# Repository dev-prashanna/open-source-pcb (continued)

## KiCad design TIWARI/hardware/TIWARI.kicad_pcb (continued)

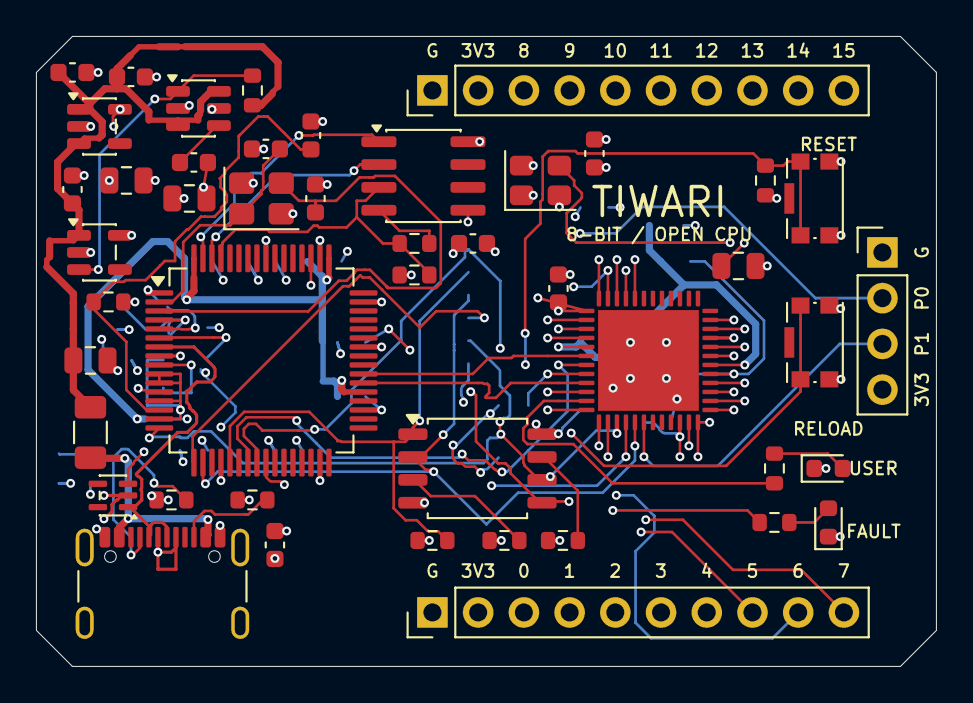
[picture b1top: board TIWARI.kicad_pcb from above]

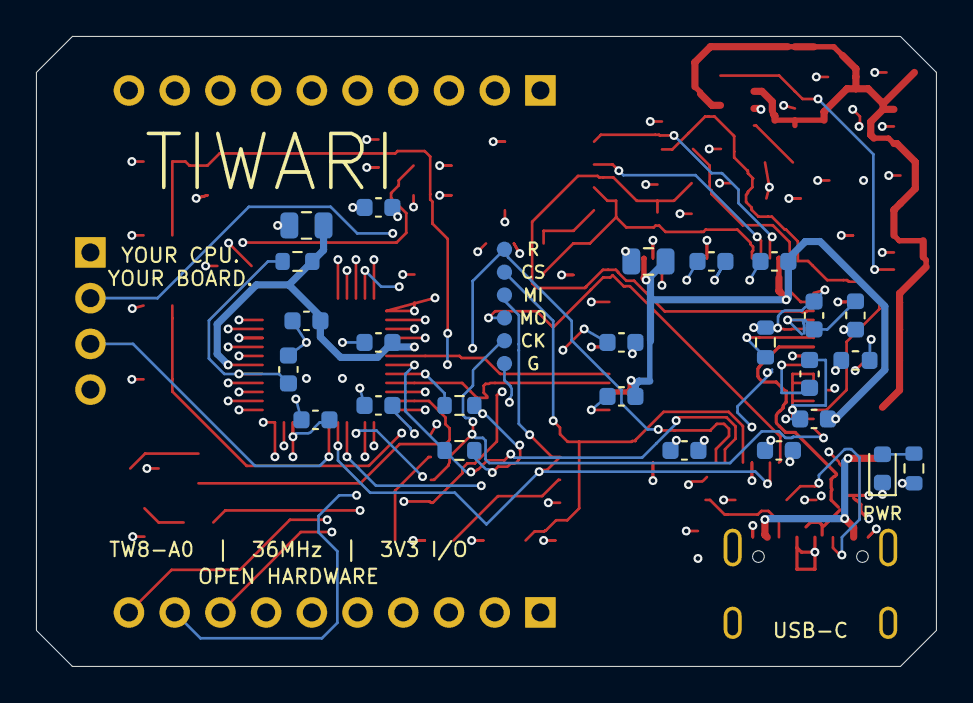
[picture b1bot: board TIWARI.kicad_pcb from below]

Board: 4 copper layers, 50.0 x 35.0 mm, 72 parts (26 on the bottom side), 58 nets.

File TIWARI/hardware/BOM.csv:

Reference,Value,MPN,Manufacturer,Footprint,Section,Datasheet
J1,USB4105-GF-A,USB4105-GF-A,GCT,Connector_USB:USB_C_Receptacle_GCT_USB4105-xx-A_16P_TopMnt_Horizontal,USB-C and Sequenced Power,https://gct.co/connector/usb4105
R1,5.1k,RC0603FR-075K1L,Yageo,Resistor_SMD:R_0603_1608Metric,USB-C and Sequenced Power,
R2,5.1k,RC0603FR-075K1L,Yageo,Resistor_SMD:R_0603_1608Metric,USB-C and Sequenced Power,
F1,500mA,1206L050YR,Littelfuse,Fuse:Fuse_1206_3216Metric,USB-C and Sequenced Power,
U3,AP2112K-1.2TRG1,AP2112K-1.2TRG1,Diodes Incorporated,Package_TO_SOT_SMD:SOT-23-5,USB-C and Sequenced Power,https://www.diodes.com/datasheet/download/AP2112.pdf
U4,AP2112K-3.3TRG1,AP2112K-3.3TRG1,Diodes Incorporated,Package_TO_SOT_SMD:SOT-23-5,USB-C and Sequenced Power,https://www.diodes.com/datasheet/download/AP2112.pdf
U5,TPS3808G12DBVR,TPS3808G12DBVR,Texas Instruments,Package_TO_SOT_SMD:SOT-23-6,USB-C and Sequenced Power,https://www.ti.com/lit/ds/symlink/tps3808.pdf
R3,10k,RC0603FR-0710KL,Yageo,Resistor_SMD:R_0603_1608Metric,USB-C and Sequenced Power,
C1,10n,GRM188R71H103KA01D,Murata,Capacitor_SMD:C_0603_1608Metric,USB-C and Sequenced Power,
C2,1u,GRM188R61A105KA61D,Murata,Capacitor_SMD:C_0603_1608Metric,USB-C and Sequenced Power,
C3,4.7u,GRM21BR61A475KA73L,Murata,Capacitor_SMD:C_0805_2012Metric,USB-C and Sequenced Power,
C4,1u,GRM188R61A105KA61D,Murata,Capacitor_SMD:C_0603_1608Metric,USB-C and Sequenced Power,
C5,4.7u,GRM21BR61A475KA73L,Murata,Capacitor_SMD:C_0805_2012Metric,USB-C and Sequenced Power,
C6,100n,GRM188R71C104KA01D,Murata,Capacitor_SMD:C_0603_1608Metric,USB-C and Sequenced Power,
C7,4.7u,GRM21BR61A475KA73L,Murata,Capacitor_SMD:C_0805_2012Metric,USB-C and Sequenced Power,
U6,TPD2E2U06DCKR,TPD2E2U06DCKR,Texas Instruments,Package_TO_SOT_SMD:SOT-353_SC-70-5,USB-C and Sequenced Power,https://www.ti.com/lit/ds/symlink/tpd2e2u06.pdf
U2,FT2232HL-REEL,FT2232HL-REEL,FTDI,Package_QFP:LQFP-64_10x10mm_P0.5mm,USB Programmer and Serial,https://www.ftdichip.cn/Support/Documents/DataSheets/ICs/DS_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
Y1,12MHz,ABM8-12.000MHZ-B2-T,Abracon,Crystal:Crystal_SMD_3225-4Pin_3.2x2.5mm,USB Programmer and Serial,
C8,27p,GRM1885C1H270JA01D,Murata,Capacitor_SMD:C_0603_1608Metric,USB Programmer and Serial,
C9,27p,GRM1885C1H270JA01D,Murata,Capacitor_SMD:C_0603_1608Metric,USB Programmer and Serial,
R4,12k,RC0603FR-0712KL,Yageo,Resistor_SMD:R_0603_1608Metric,USB Programmer and Serial,
R5,10k,RC0603FR-0710KL,Yageo,Resistor_SMD:R_0603_1608Metric,USB Programmer and Serial,
C10,100n,GRM188R71C104KA01D,Murata,Capacitor_SMD:C_0603_1608Metric,USB Programmer and Serial,
FB1,600R@100MHz,BLM18AG601SN1D,Murata,Inductor_SMD:L_0603_1608Metric,USB Programmer and Serial,
FB2,600R@100MHz,BLM18AG601SN1D,Murata,Inductor_SMD:L_0603_1608Metric,USB Programmer and Serial,
C11,100n,GRM188R71C104KA01D,Murata,Capacitor_SMD:C_0603_1608Metric,USB Programmer and Serial,
C12,100n,GRM188R71C104KA01D,Murata,Capacitor_SMD:C_0603_1608Metric,USB Programmer and Serial,
C13,100n,GRM188R71C104KA01D,Murata,Capacitor_SMD:C_0603_1608Metric,USB Programmer and Serial,
C14,100n,GRM188R71C104KA01D,Murata,Capacitor_SMD:C_0603_1608Metric,USB Programmer and Serial,
C15,100n,GRM188R71C104KA01D,Murata,Capacitor_SMD:C_0603_1608Metric,USB Programmer and Serial,
C16,100n,GRM188R71C104KA01D,Murata,Capacitor_SMD:C_0603_1608Metric,USB Programmer and Serial,
C17,100n,GRM188R71C104KA01D,Murata,Capacitor_SMD:C_0603_1608Metric,USB Programmer and Serial,
C18,100n,GRM188R71C104KA01D,Murata,Capacitor_SMD:C_0603_1608Metric,USB Programmer and Serial,
C19,100n,GRM188R71C104KA01D,Murata,Capacitor_SMD:C_0603_1608Metric,USB Programmer and Serial,
C20,4.7u,GRM21BR61A475KA73L,Murata,Capacitor_SMD:C_0805_2012Metric,USB Programmer and Serial,
C21,1u,GRM188R61A105KA61D,Murata,Capacitor_SMD:C_0603_1608Metric,USB Programmer and Serial,
U8,93LC46BT-I/SN,93LC46BT-I/SN,Microchip,Package_SO:SOIC-8_3.9x4.9mm_P1.27mm,USB Programmer and Serial,https://ww1.microchip.com/downloads/en/DeviceDoc/20001749K.pdf
R6,2.2k,RC0603FR-072K2L,Yageo,Resistor_SMD:R_0603_1608Metric,USB Programmer and Serial,
R7,10k,RC0603FR-0710KL,Yageo,Resistor_SMD:R_0603_1608Metric,USB Programmer and Serial,
C22,100n,GRM188R71C104KA01D,Murata,Capacitor_SMD:C_0603_1608Metric,USB Programmer and Serial,
U1,ICE40UP5K-SG48ITR,ICE40UP5K-SG48ITR,Lattice Semiconductor,TIWARI:UP5K_SG48_Reviewed,TIWARI CPU Fabric,https://www.latticesemi.com/api/document/download?id=51968
U7,W25Q32JVSSIQ,W25Q32JVSSIQ,Winbond,Package_SO:SOIC-8_5.3x5.3mm_P1.27mm,TIWARI CPU Fabric,https://www.winbond.com/resource-files/w25q32jv%20spi%20revg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
Y2,12MHz 3V3 CMOS,ASE-12.000MHZ-LC-T,Abracon,Oscillator:Oscillator_SMD_Abracon_ASE-4Pin_3.2x2.5mm,TIWARI CPU Fabric,https://abracon.com/Oscillators/ASE.pdf
C23,100n,GRM188R71C104KA01D,Murata,Capacitor_SMD:C_0603_1608Metric,TIWARI CPU Fabric,
R8,10k,RC0603FR-0710KL,Yageo,Resistor_SMD:R_0603_1608Metric,TIWARI CPU Fabric,
R9,10k,RC0603FR-0710KL,Yageo,Resistor_SMD:R_0603_1608Metric,TIWARI CPU Fabric,
R10,100,RC0603FR-07100RL,Yageo,Resistor_SMD:R_0603_1608Metric,TIWARI CPU Fabric,
C24,1u,GRM188R61A105KA61D,Murata,Capacitor_SMD:C_0603_1608Metric,TIWARI CPU Fabric,
C25,100n,GRM188R71C104KA01D,Murata,Capacitor_SMD:C_0603_1608Metric,TIWARI CPU Fabric,
C26,100n,GRM188R71C104KA01D,Murata,Capacitor_SMD:C_0603_1608Metric,TIWARI CPU Fabric,
C27,100n,GRM188R71C104KA01D,Murata,Capacitor_SMD:C_0603_1608Metric,TIWARI CPU Fabric,
C28,100n,GRM188R71C104KA01D,Murata,Capacitor_SMD:C_0603_1608Metric,TIWARI CPU Fabric,
C29,100n,GRM188R71C104KA01D,Murata,Capacitor_SMD:C_0603_1608Metric,TIWARI CPU Fabric,
C30,100n,GRM188R71C104KA01D,Murata,Capacitor_SMD:C_0603_1608Metric,TIWARI CPU Fabric,
C31,4.7u,GRM21BR61A475KA73L,Murata,Capacitor_SMD:C_0805_2012Metric,TIWARI CPU Fabric,
C32,4.7u,GRM21BR61A475KA73L,Murata,Capacitor_SMD:C_0805_2012Metric,TIWARI CPU Fabric,
R11,10k,RC0603FR-0710KL,Yageo,Resistor_SMD:R_0603_1608Metric,TIWARI CPU Fabric,
R12,10k,RC0603FR-0710KL,Yageo,Resistor_SMD:R_0603_1608Metric,TIWARI CPU Fabric,
R13,10k,RC0603FR-0710KL,Yageo,Resistor_SMD:R_0603_1608Metric,TIWARI CPU Fabric,
R14,10k,RC0603FR-0710KL,Yageo,Resistor_SMD:R_0603_1608Metric,TIWARI CPU Fabric,
SW1,CPU RESET,KMR221GLFS,C&K,Button_Switch_SMD:SW_Push_1P1T-SH_NO_CK_KMR2xxG,TIWARI CPU Fabric,
SW2,RECONFIGURE,KMR221GLFS,C&K,Button_Switch_SMD:SW_Push_1P1T-SH_NO_CK_KMR2xxG,TIWARI CPU Fabric,
J2,J2 / 3V3 ONLY,61301011121,Wurth Elektronik,Connector_PinHeader_2.54mm:PinHeader_1x10_P2.54mm_Vertical,Expansion and Indicators,
J3,J3 / 3V3 ONLY,61301011121,Wurth Elektronik,Connector_PinHeader_2.54mm:PinHeader_1x10_P2.54mm_Vertical,Expansion and Indicators,
J4,J4 / 3V3 ONLY,61300411121,Wurth Elektronik,Connector_PinHeader_2.54mm:PinHeader_1x04_P2.54mm_Vertical,Expansion and Indicators,
R15,1k,RC0603FR-071KL,Yageo,Resistor_SMD:R_0603_1608Metric,Expansion and Indicators,
D1,POWER,LTST-C190KGKT,Lite-On,LED_SMD:LED_0603_1608Metric,Expansion and Indicators,
R16,1k,RC0603FR-071KL,Yageo,Resistor_SMD:R_0603_1608Metric,Expansion and Indicators,
D2,USER,LTST-C190KGKT,Lite-On,LED_SMD:LED_0603_1608Metric,Expansion and Indicators,
R17,1k,RC0603FR-071KL,Yageo,Resistor_SMD:R_0603_1608Metric,Expansion and Indicators,
D3,FAULT,LTST-C190KRKT,Lite-On,LED_SMD:LED_0603_1608Metric,Expansion and Indicators,

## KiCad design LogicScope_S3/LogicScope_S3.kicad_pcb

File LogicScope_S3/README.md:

# LogicScope S3 — LS-S3-A0

Compact 8-channel USB digital logic analyzer hardware by Prashanna Tiwari.
Open `LogicScope_S3.kicad_pro` in KiCad 10. The project contains native
hierarchical schematics, verified library parts and an actual two-layer PCB.

**Engineering prototype; firmware and desktop software v0.1.0 are implemented
but not bench validated.** 1 MS/s is an unmeasured finite-capture target,
not an advertised continuous rate. There is no analog voltage measurement.

## Design

- ESP32-S3-WROOM-1-N8R2, eight parallel LCD_CAM inputs and GDMA.
- SN74LVC245APW at 3.3 V with 5.5-V-tolerant inputs, 220-ohm series resistors
  and 100-kilohm input pull-downs. External signal range: 0–5 V.
- USB-C device port, native USB Full-Speed, ESD protection and 3.3-V buck supply.
- Two 2x5 input headers, BOOT/RESET, capture/power LEDs and UART/test access.
- 55 x 40 mm, two layers, 0.8-mm board; PCB antenna overhangs by 6.75 mm.
- **TIWARI** etched in front copper and printed on silkscreen.

Use a common ground with the target. J2 pin 7 is a current-limited reference
only; this instrument does not power the target.

## Firmware and desktop software

- [ESP32-S3 firmware: build, flash and capture behavior](firmware/README.md)
- [Simple desktop app: setup and usage](software/README.md)
- [USB protocol](docs/USB_Protocol.md)
- [Software verification and remaining hardware checks](docs/Software_Verification.md)

Firmware uses LCD_CAM/GDMA with the PCB's GPIO12-to-GPIO11 sampling-clock
loopback. Select 100 kS/s, 250 kS/s, 500 kS/s or 1 MS/s and collect up to
65,536 packed eight-channel samples before uploading over USB. All rates
remain unmeasured. Trigger search marks a matching event within a finite
capture; rolling pre-trigger history and continuous streaming are not enabled.

The Python/Tk app includes eight waveform lanes, zoom/pan, timing cursors,
save/open, CSV/VCD export, and a synthetic demo mode. From `software/`:

```sh
python3 -m venv .venv
. .venv/bin/activate
python -m pip install -e .
logicscope --demo
```

## Files and limitations

Read [acquisition architecture](docs/Acquisition_Architecture.md),
[electrical/fabrication decisions](docs/Electrical_and_Fabrication.md) and the
[hardware validation plan](docs/Validation_Plan.md) before ordering or using
a prototype. Connector pinout and GPIO allocation are supplied as CSV files.
`BOM.csv` contains exact manufacturer part numbers and DNP status.

Final checks: ERC 0, DRC 0, unconnected nets 0, schematic parity findings 0.
Read the [engineering report](docs/Engineering_Report.md). Manufacturing files
are in `fabrication/`; the KiCad 3D render is in `previews/`.

Fabrication needs a stack-specific USB impedance review and the documented
USB connector hole-clearance capability. Sampling, USB throughput, power,
thermal and ESD behavior require physical prototype testing.

## Tool workflow

Connected KiCad MCP created the native project and initial components,
generated a netlist and ran electrical checks. Native pcbnew scripts perform
placement and routing because those editing operations are absent from the
connected MCP. Native KiCad CLI and MCP perform final validation and exports.
Scripts under `scripts/` record engineering operations; do not run placement
or initial-routing scripts over the completed board. `release.py`, when
available, validates the current design and exports without reconstructing it.

Copyright (c) 2026 Prashanna Tiwari. Hardware: [CERN-OHL-P-2.0](LICENSE).
Firmware and desktop app: MIT (see their respective directories).
KiCad-derived library graphics retain their upstream licence in `libraries/`.

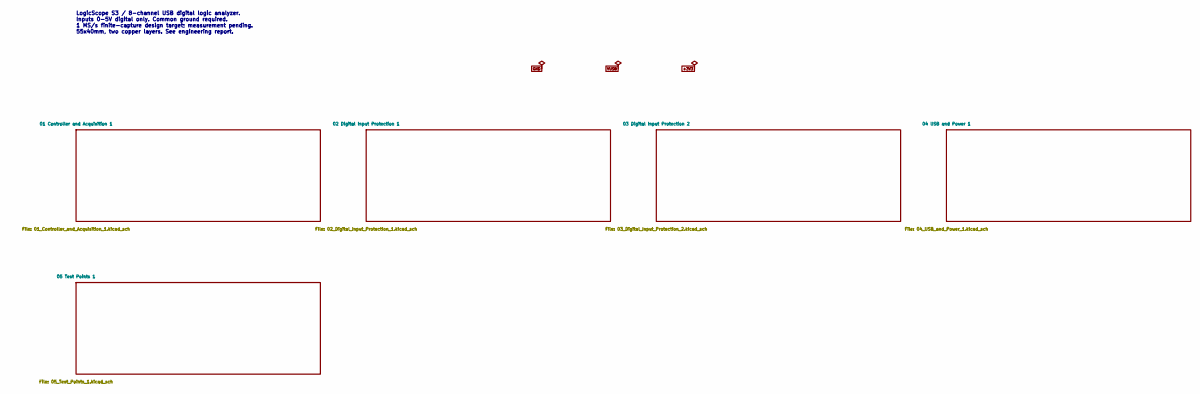
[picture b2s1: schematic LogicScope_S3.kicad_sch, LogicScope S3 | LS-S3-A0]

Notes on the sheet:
LogicScope S3 / 8-channel USB digital logic analyzer. Inputs 0-5V digital only. Common ground required. 1 MS/s finite-capture design target; measurement pending. 55x40mm, two copper layers. See engineering report.

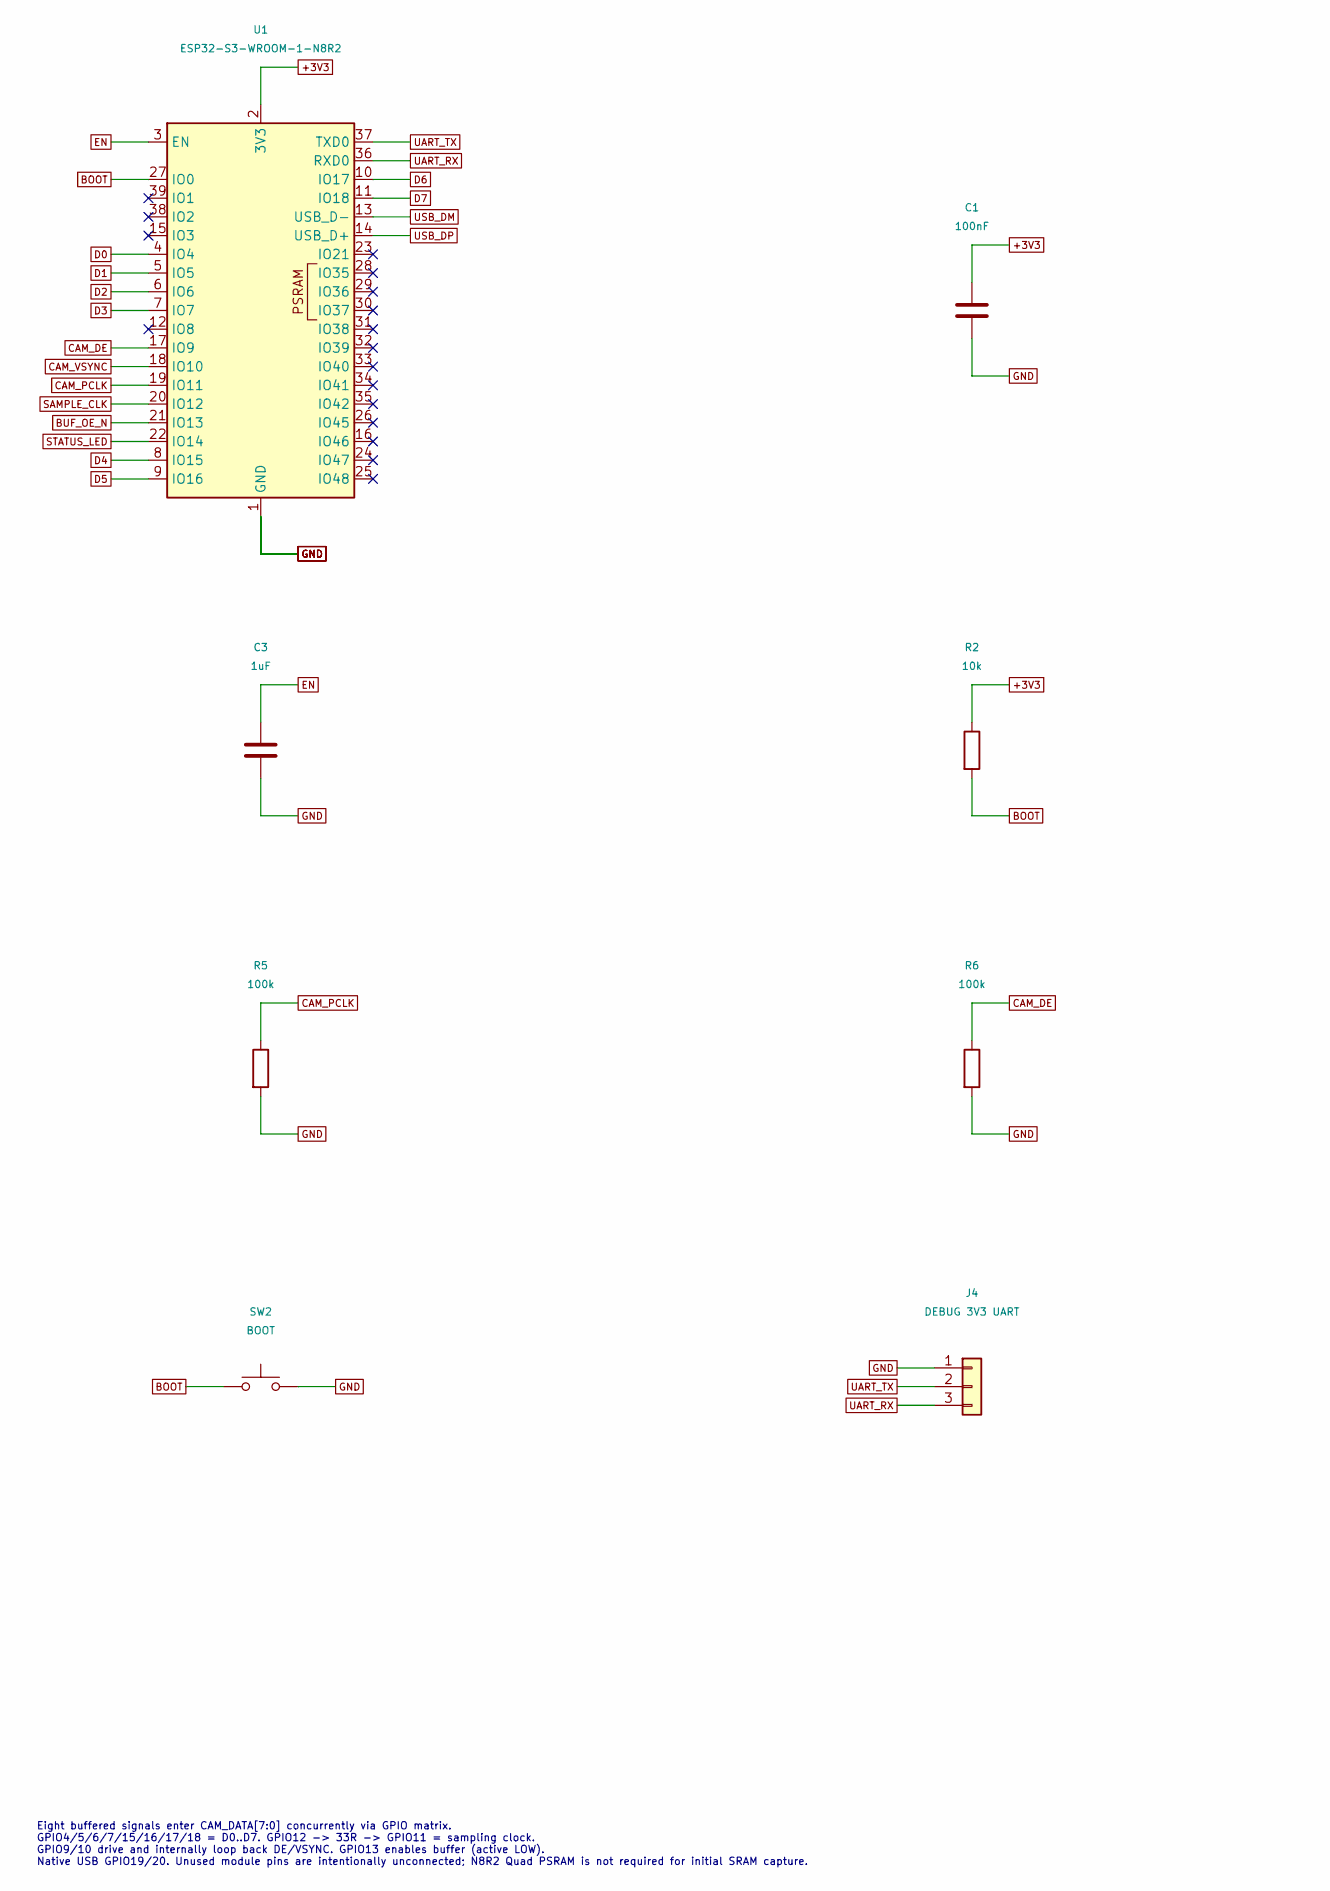
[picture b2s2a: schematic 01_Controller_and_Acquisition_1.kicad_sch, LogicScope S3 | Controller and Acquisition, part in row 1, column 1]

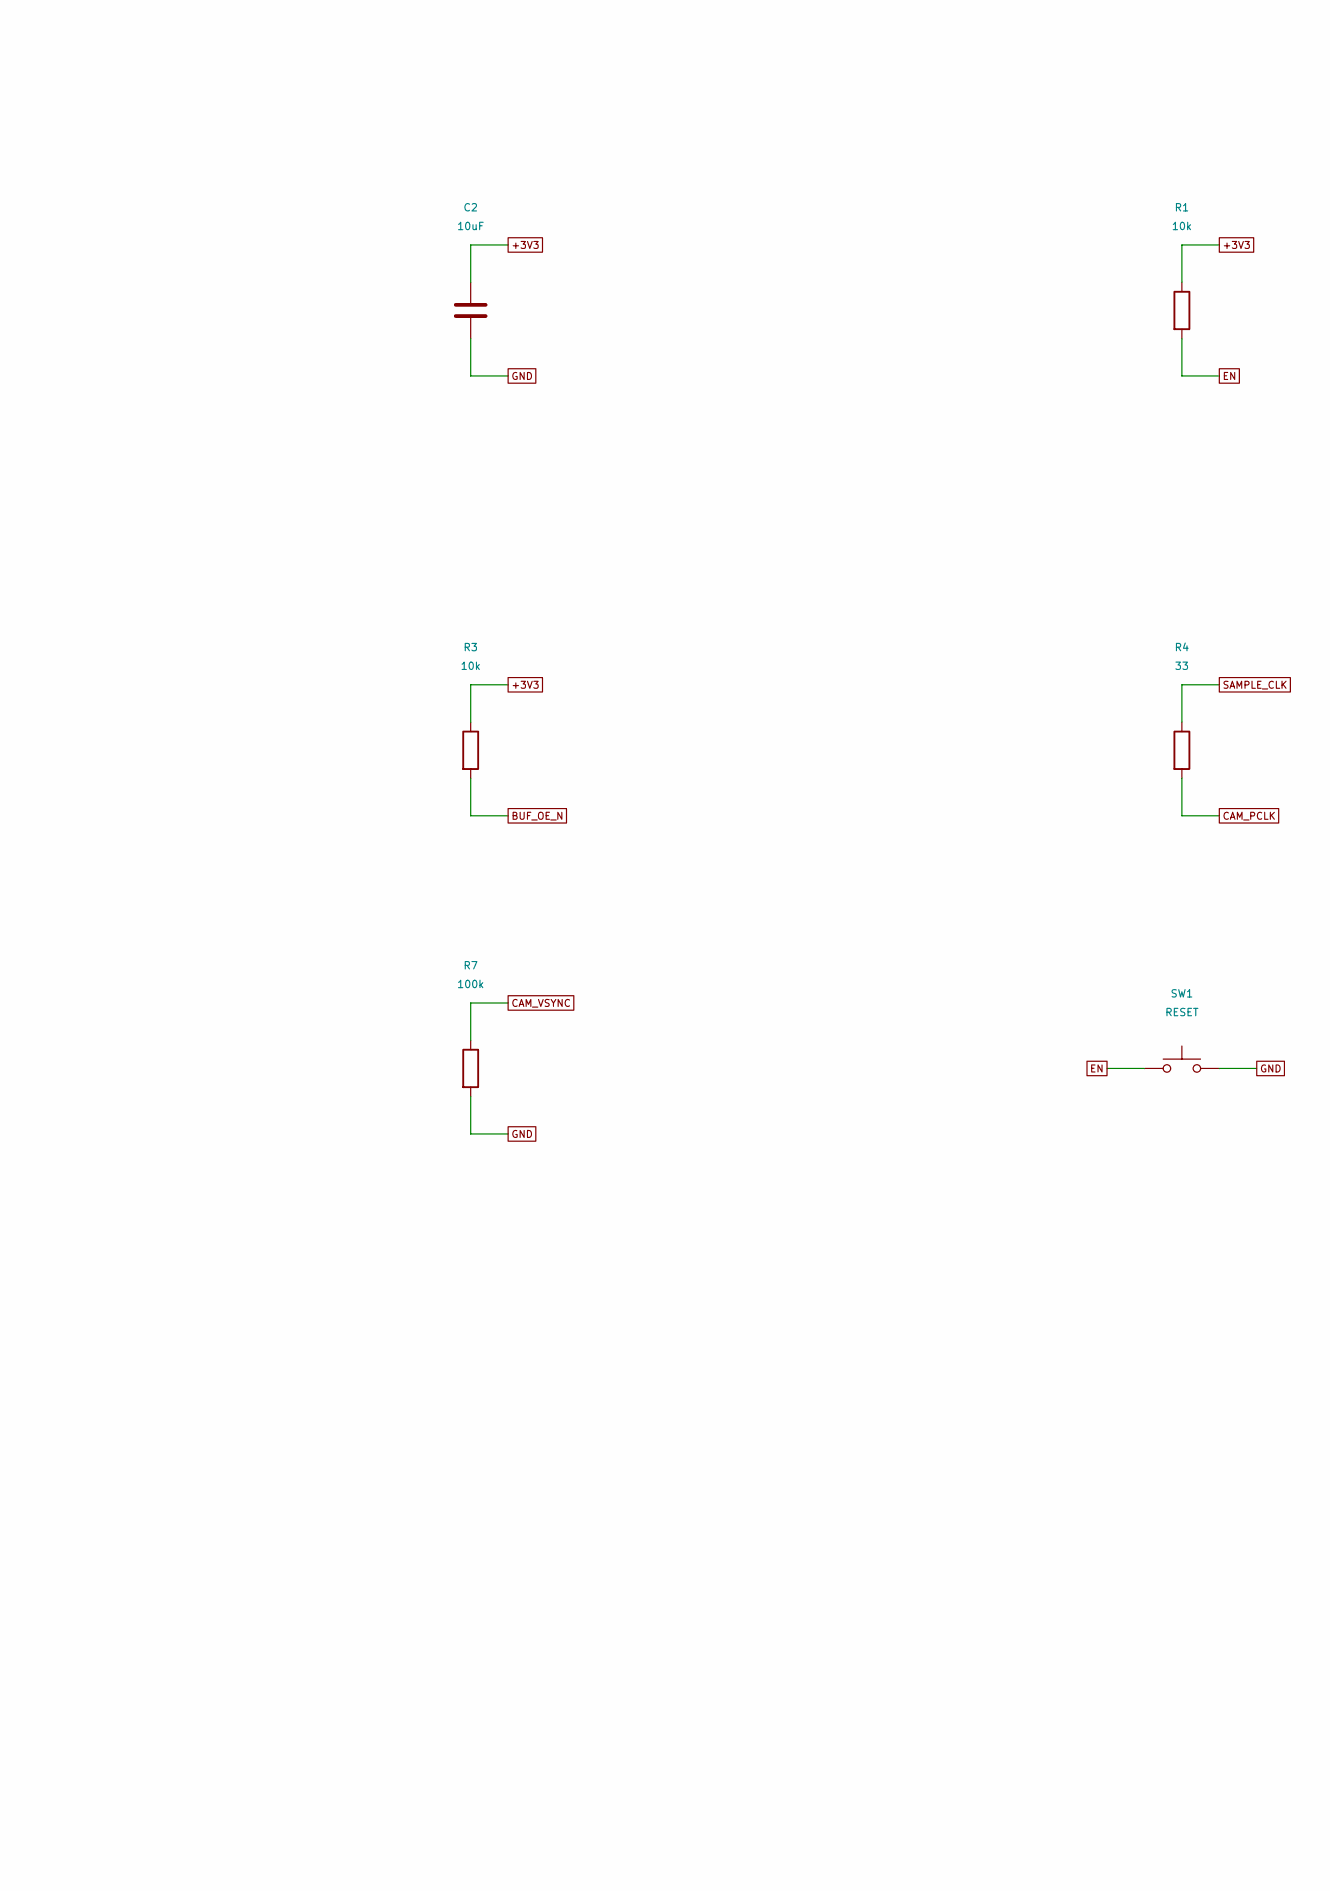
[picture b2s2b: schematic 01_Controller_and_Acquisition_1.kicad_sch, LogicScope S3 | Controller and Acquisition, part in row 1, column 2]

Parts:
C1: 100nF; C_0603_1608Metric; MPN GRM188R71C104KA01D
C2: 10uF; C_0805_2012Metric; MPN GRM21BR61A106KE19L
C3: 1uF; C_0603_1608Metric; MPN GRM188R61A105KA61D
J4: DEBUG 3V3 UART; PinHeader_1x03_P2.54mm_Vertical; MPN 61300311121
R1, R2, R3: 10k; R_0603_1608Metric; MPN RC0603FR-0710KL
R4: 33; R_0603_1608Metric; MPN RC0603FR-0733RL
R5, R6, R7: 100k; R_0603_1608Metric; MPN RC0603FR-07100KL
SW1: RESET; SW_Push_1P1T-SH_NO_CK_KMR2xxG; MPN KMR221GLFS
SW2: BOOT; SW_Push_1P1T-SH_NO_CK_KMR2xxG; MPN KMR221GLFS
U1: ESP32-S3-WROOM-1-N8R2; ESP32-S3-WROOM-1_Overhang; MPN ESP32-S3-WROOM-1-N8R2

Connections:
+3V3: C1.1, C2.1, R1.1, R2.1, R3.1, U1.2 (3V3); also elsewhere on the board
BOOT: R2.2, SW2.1, U1.27 (IO0)
BUF_OE_N: R3.2, U1.21 (IO13); also elsewhere on the board
CAM_DE: R6.1, U1.17 (IO9); also elsewhere on the board
CAM_PCLK: R4.2, R5.1, U1.19 (IO11); also elsewhere on the board
CAM_VSYNC: R7.1, U1.18 (IO10); also elsewhere on the board
D0: U1.4 (IO4); also elsewhere on the board
D1: U1.5 (IO5); also elsewhere on the board
D2: U1.6 (IO6); also elsewhere on the board
D3: U1.7 (IO7); also elsewhere on the board
D4: U1.8 (IO15); also elsewhere on the board
D5: U1.9 (IO16); also elsewhere on the board
D6: U1.10 (IO17); also elsewhere on the board
D7: U1.11 (IO18); also elsewhere on the board
EN: C3.1, R1.2, SW1.1, U1.3 (EN); also elsewhere on the board
GND: C1.2, C2.2, C3.2, J4.1, R5.2, R6.2, R7.2, SW1.2, SW2.2, U1.1 (GND), U1.40 (GND), U1.41 (GND); also elsewhere on the board
SAMPLE_CLK: R4.1, U1.20 (IO12)
STATUS_LED: U1.22 (IO14); also elsewhere on the board
UART_RX: J4.3, U1.36 (RXD0)
UART_TX: J4.2, U1.37 (TXD0)
USB_DM: U1.13 (USB_D-); also elsewhere on the board
USB_DP: U1.14 (USB_D+); also elsewhere on the board

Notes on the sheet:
Eight buffered signals enter CAM_DATA[7:0] concurrently via GPIO matrix. GPIO4/5/6/7/15/16/17/18 = D0..D7. GPIO12 -> 33R -> GPIO11 = sampling clock. GPIO9/10 drive and internally loop back DE/VSYNC. GPIO13 enables buffer (active LOW). Native USB GPIO19/20. Unused module pins are intentionally uncon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

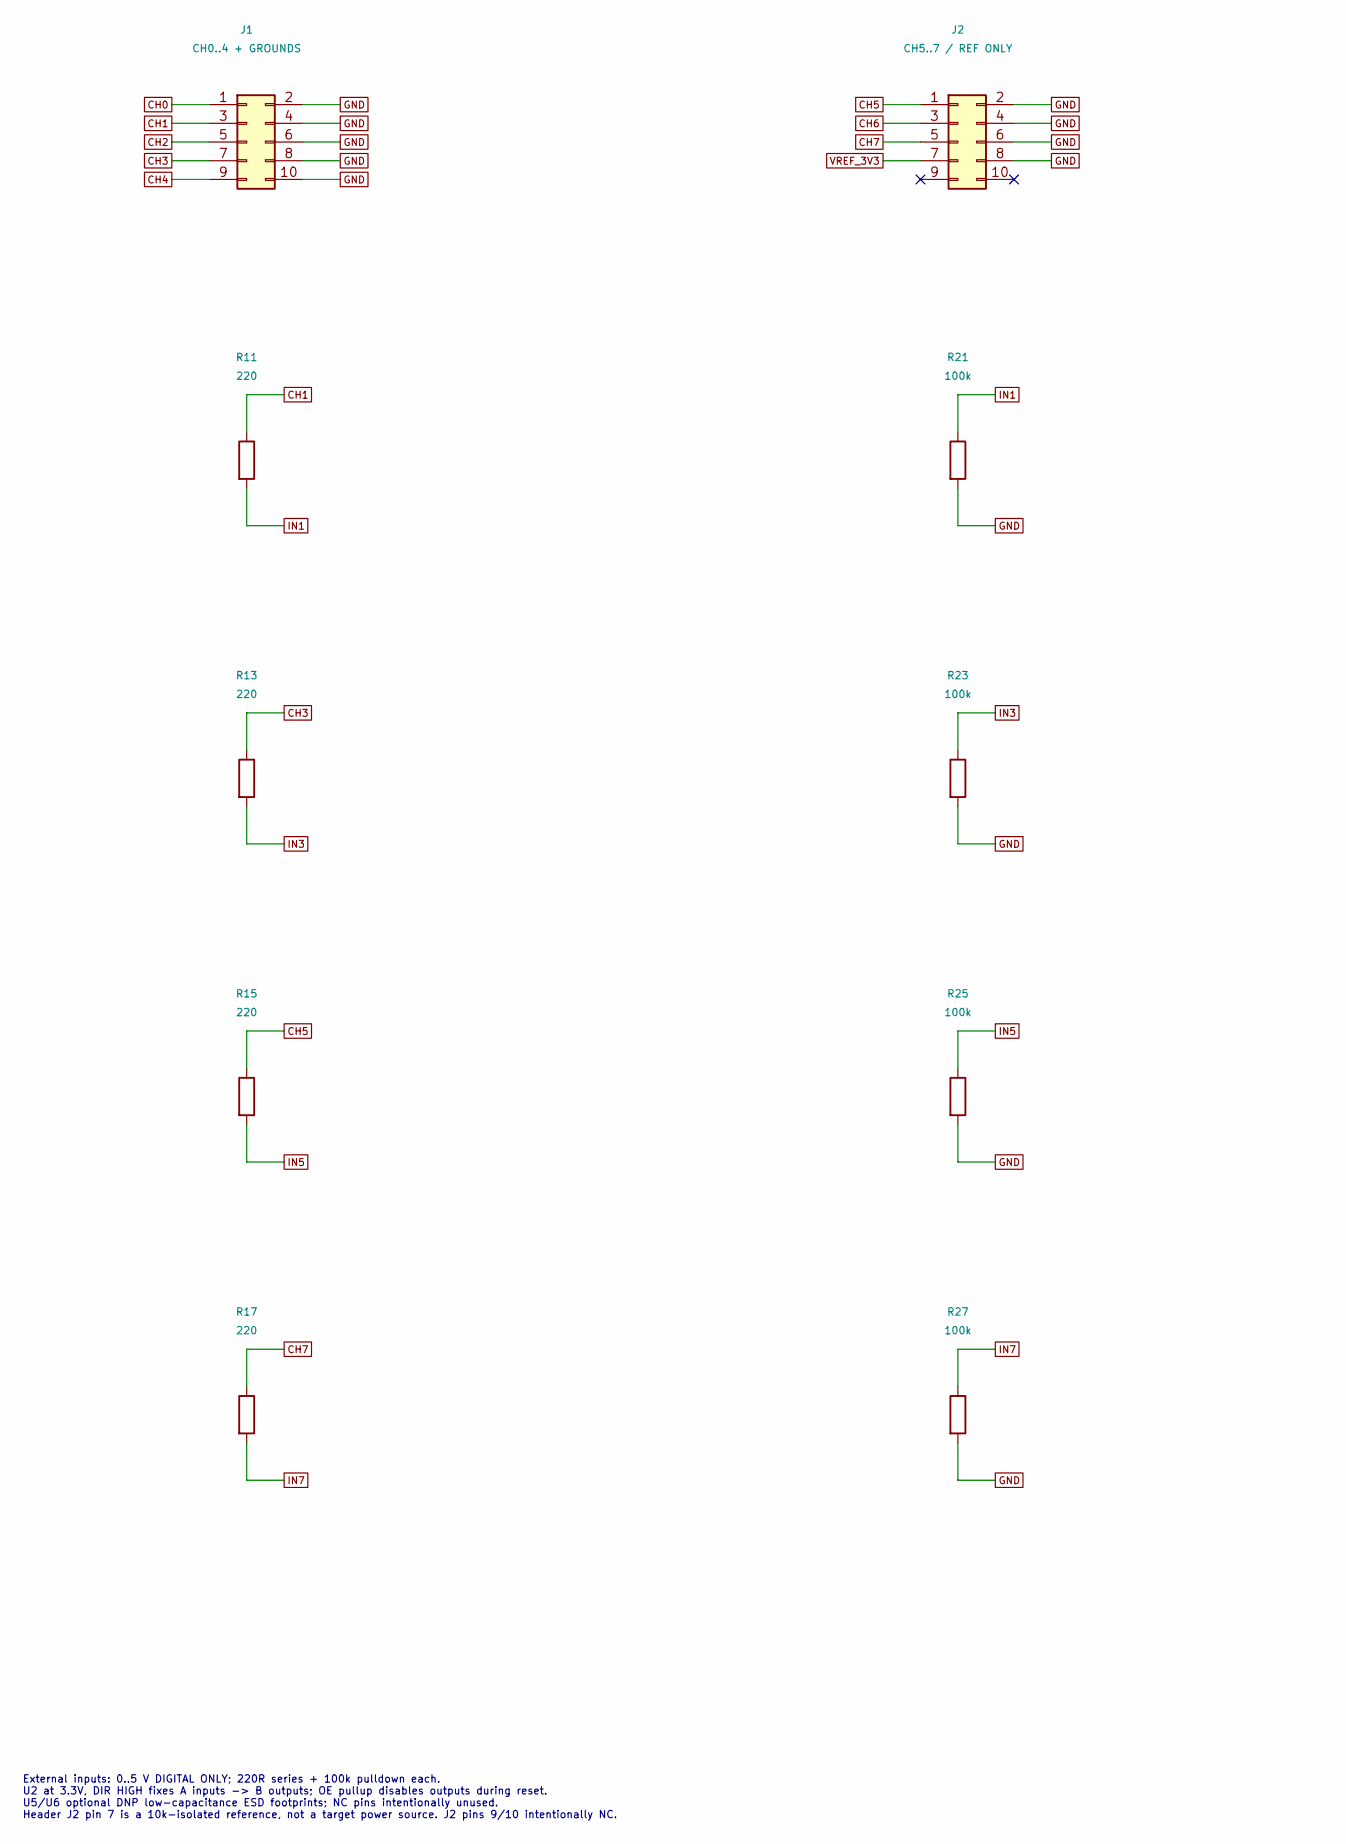
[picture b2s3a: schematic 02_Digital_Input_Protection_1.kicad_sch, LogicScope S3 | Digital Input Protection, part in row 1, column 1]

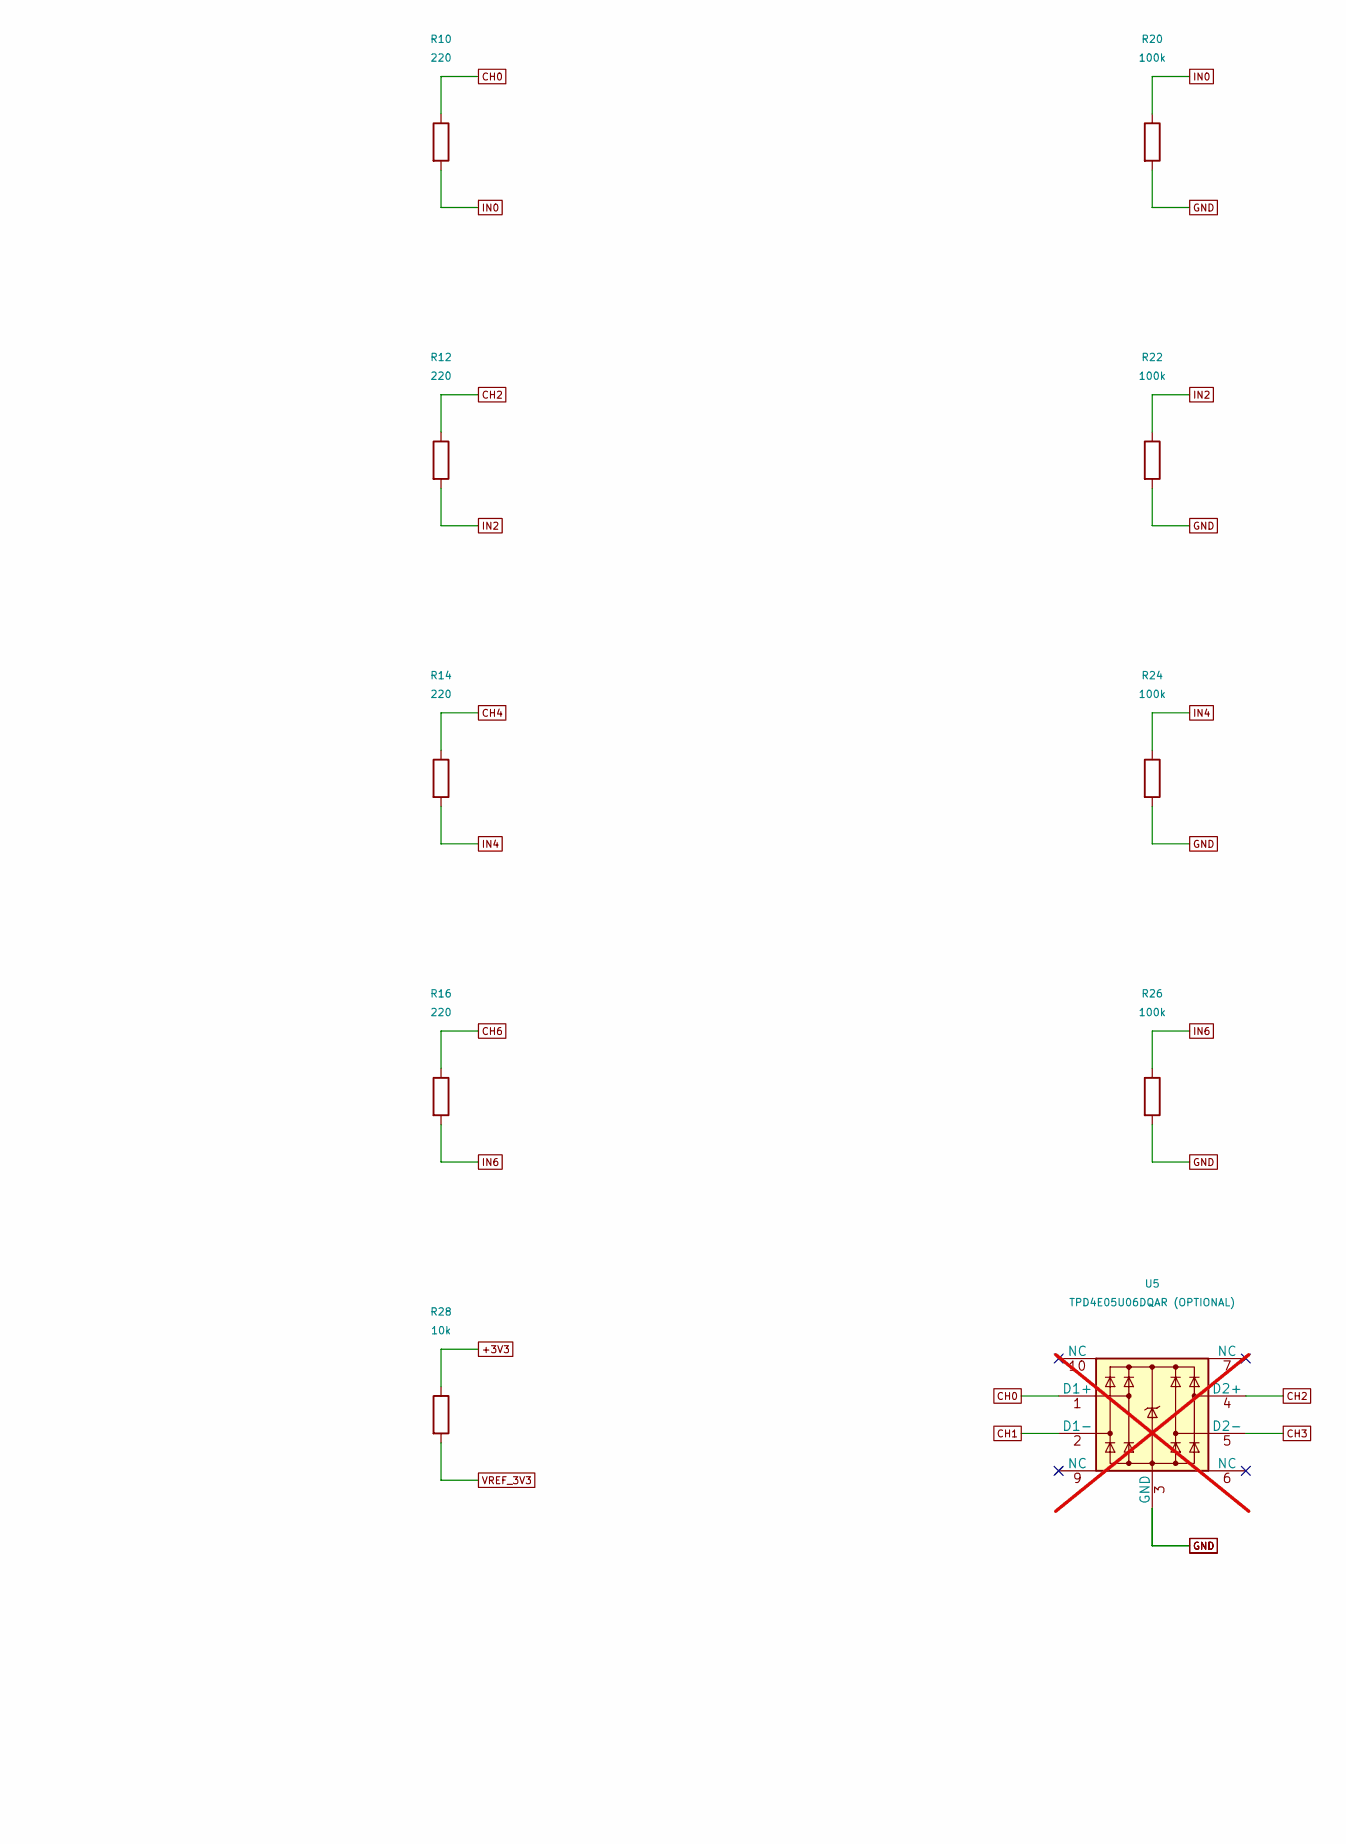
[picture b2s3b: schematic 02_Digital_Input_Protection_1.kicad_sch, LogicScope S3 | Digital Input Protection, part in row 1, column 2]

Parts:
J1: CH0..4 + GROUNDS; PinHeader_2x05_P2.54mm_Vertical; MPN 61301021121
J2: CH5..7 / REF ONLY; PinHeader_2x05_P2.54mm_Vertical; MPN 61301021121
R10, R11, R12, R13, R14, R15, R16, R17: 220; R_0603_1608Metric; MPN RC0603FR-07220RL
R20, R21, R22, R23, R24, R25, R26, R27: 100k; R_0603_1608Metric; MPN RC0603FR-07100KL
R28: 10k; R_0603_1608Metric; MPN RC0603FR-0710KL
U5: TPD4E05U06DQAR (OPTIONAL); USON-10_2.5x1.0mm_P0.5mm; MPN TPD4E05U06DQAR; not fitted

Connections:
+3V3: R28.1; also elsewhere on the board
CH0: J1.1, R10.1, U5.1 (D1+)
CH1: J1.3, R11.1, U5.2 (D1-)
CH2: J1.5, R12.1, U5.4 (D2+)
CH3: J1.7, R13.1, U5.5 (D2-)
CH4: J1.9, R14.1; also elsewhere on the board
CH5: J2.1, R15.1; also elsewhere on the board
CH6: J2.3, R16.1; also elsewhere on the board
CH7: J2.5, R17.1; also elsewhere on the board
GND: J1.2, J1.4, J1.6, J1.8, J1.10, J2.2, J2.4, J2.6, J2.8, R20.2, R21.2, R22.2, R23.2, R24.2, R25.2, R26.2, R27.2, U5.3 (GND), U5.8 (GND); also elsewhere on the board
IN0: R10.2, R20.1; also elsewhere on the board
IN1: R11.2, R21.1; also elsewhere on the board
IN2: R12.2, R22.1; also elsewhere on the board
IN3: R13.2, R23.1; also elsewhere on the board
IN4: R14.2, R24.1; also elsewhere on the board
IN5: R15.2, R25.1; also elsewhere on the board
IN6: R16.2, R26.1; also elsewhere on the board
IN7: R17.2, R27.1; also elsewhere on the board
VREF_3V3: J2.7, R28.2

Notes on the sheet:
External inputs: 0..5 V DIGITAL ONLY; 220R series + 100k pulldown each. U2 at 3.3V, DIR HIGH fixes A inputs -> B outputs; OE pullup disables outputs during reset. U5/U6 optional DNP low-capacitance ESD footprints; NC pins intentionally unused. Header J2 pin 7 is a 10k-isolated reference, not a targ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
